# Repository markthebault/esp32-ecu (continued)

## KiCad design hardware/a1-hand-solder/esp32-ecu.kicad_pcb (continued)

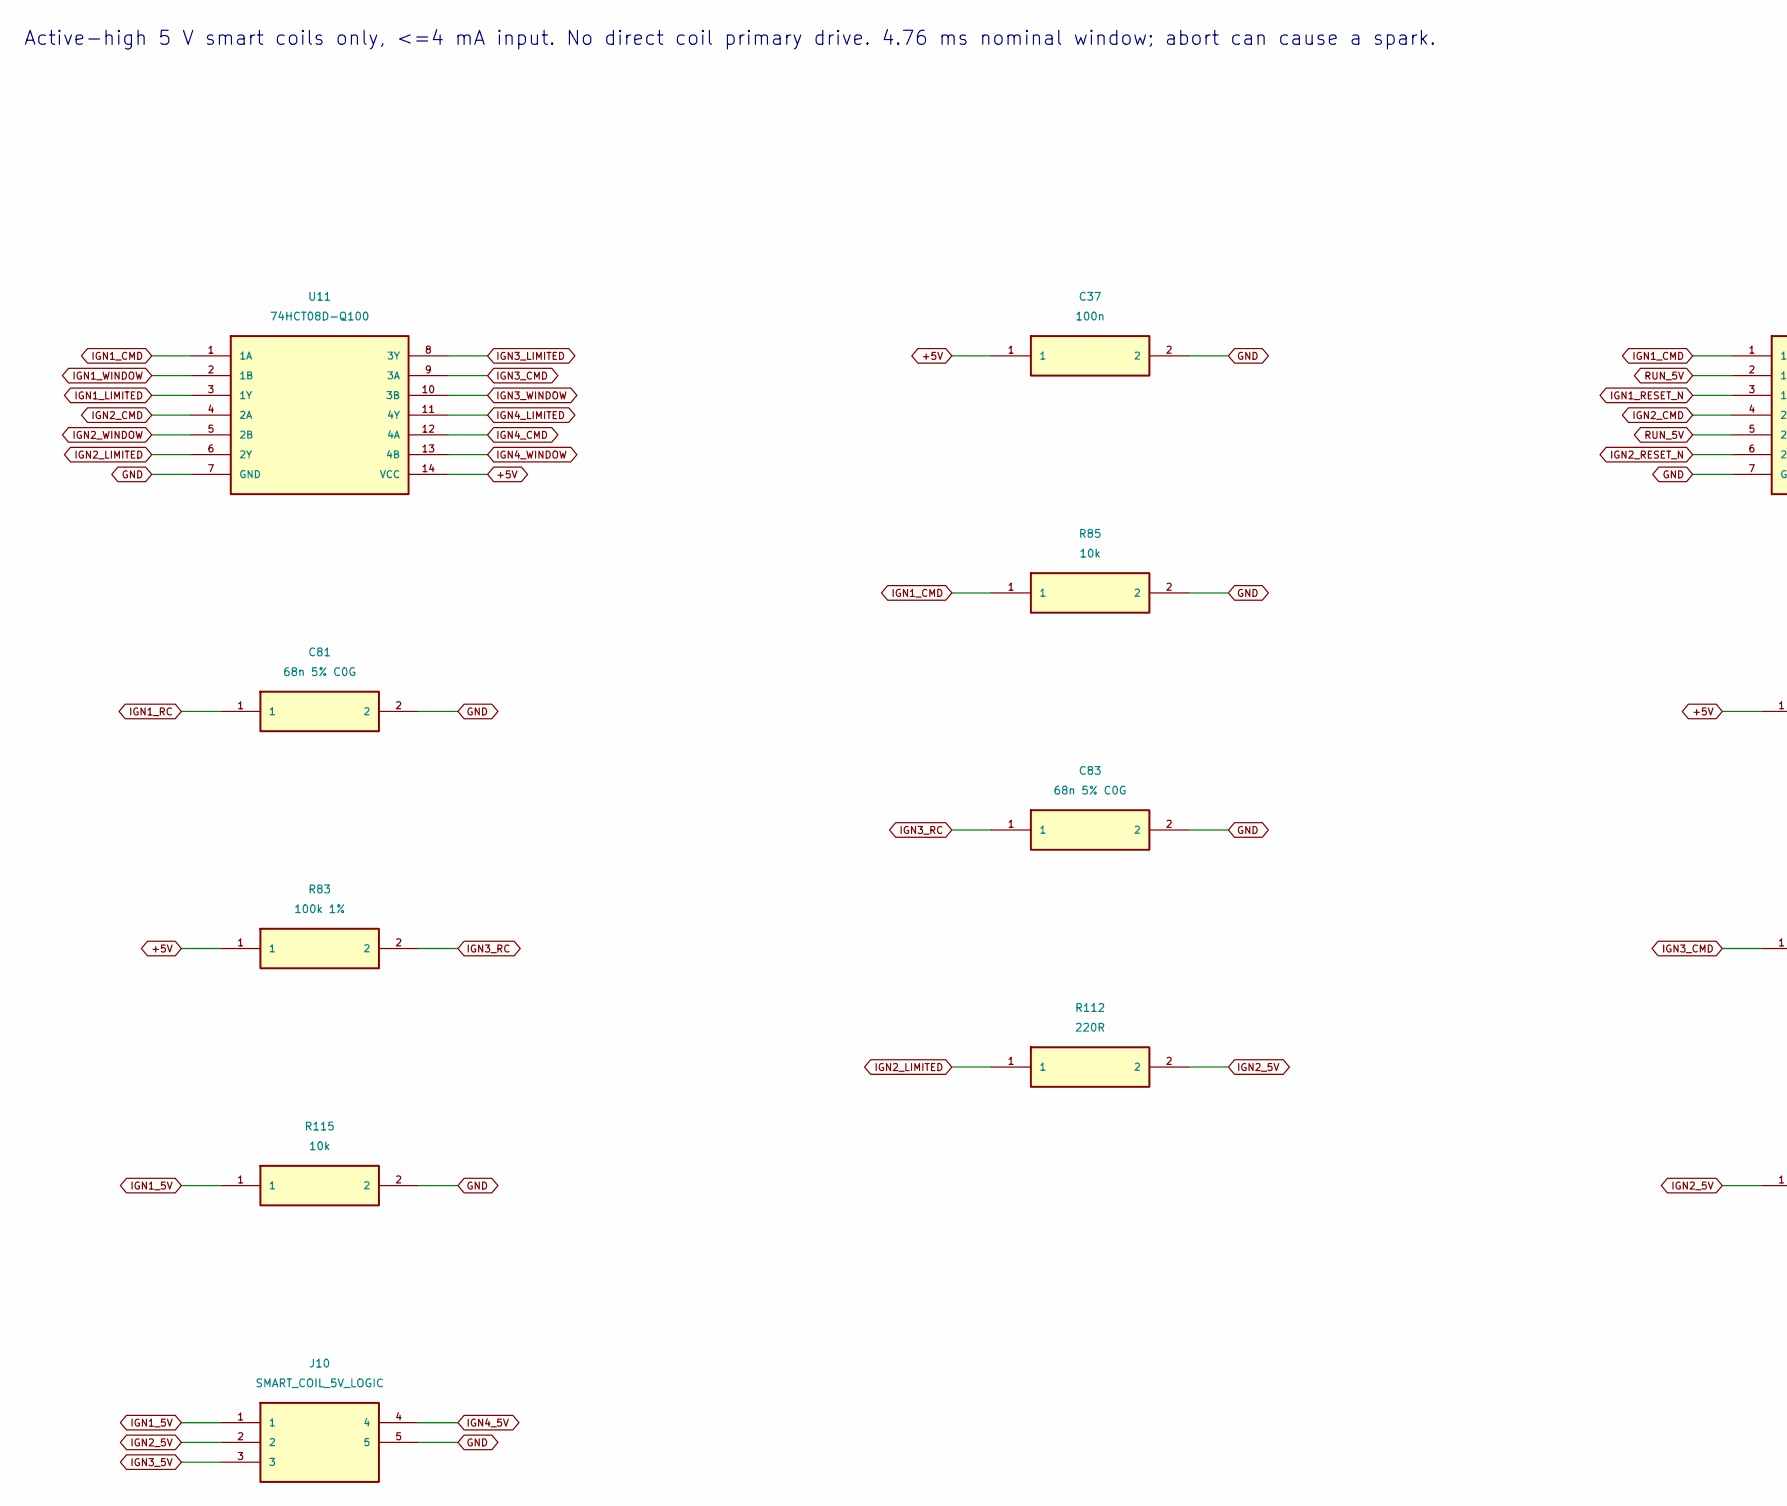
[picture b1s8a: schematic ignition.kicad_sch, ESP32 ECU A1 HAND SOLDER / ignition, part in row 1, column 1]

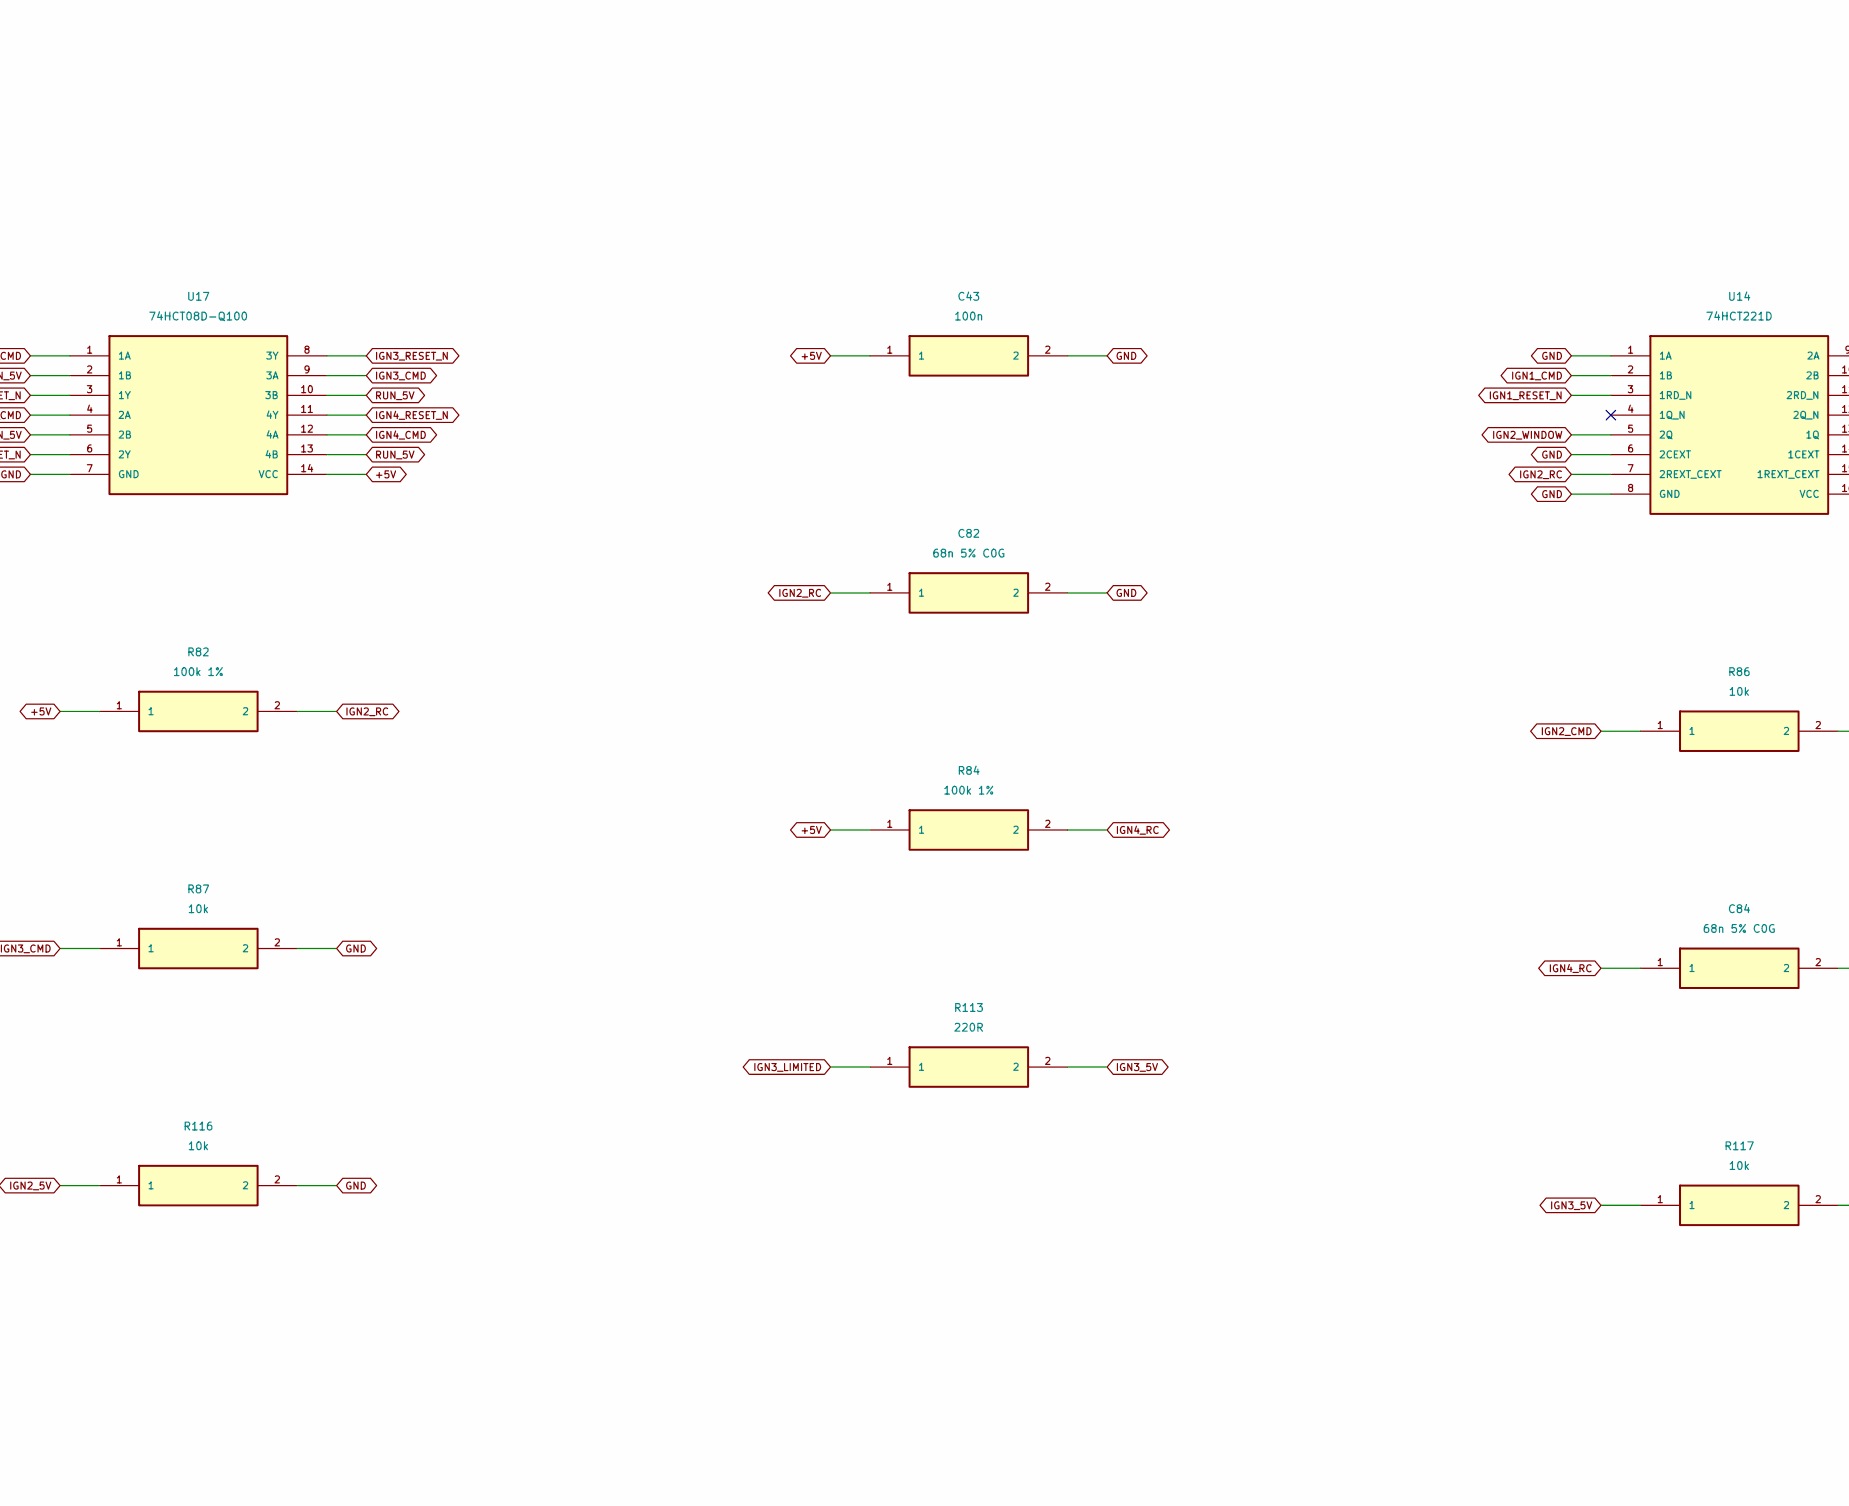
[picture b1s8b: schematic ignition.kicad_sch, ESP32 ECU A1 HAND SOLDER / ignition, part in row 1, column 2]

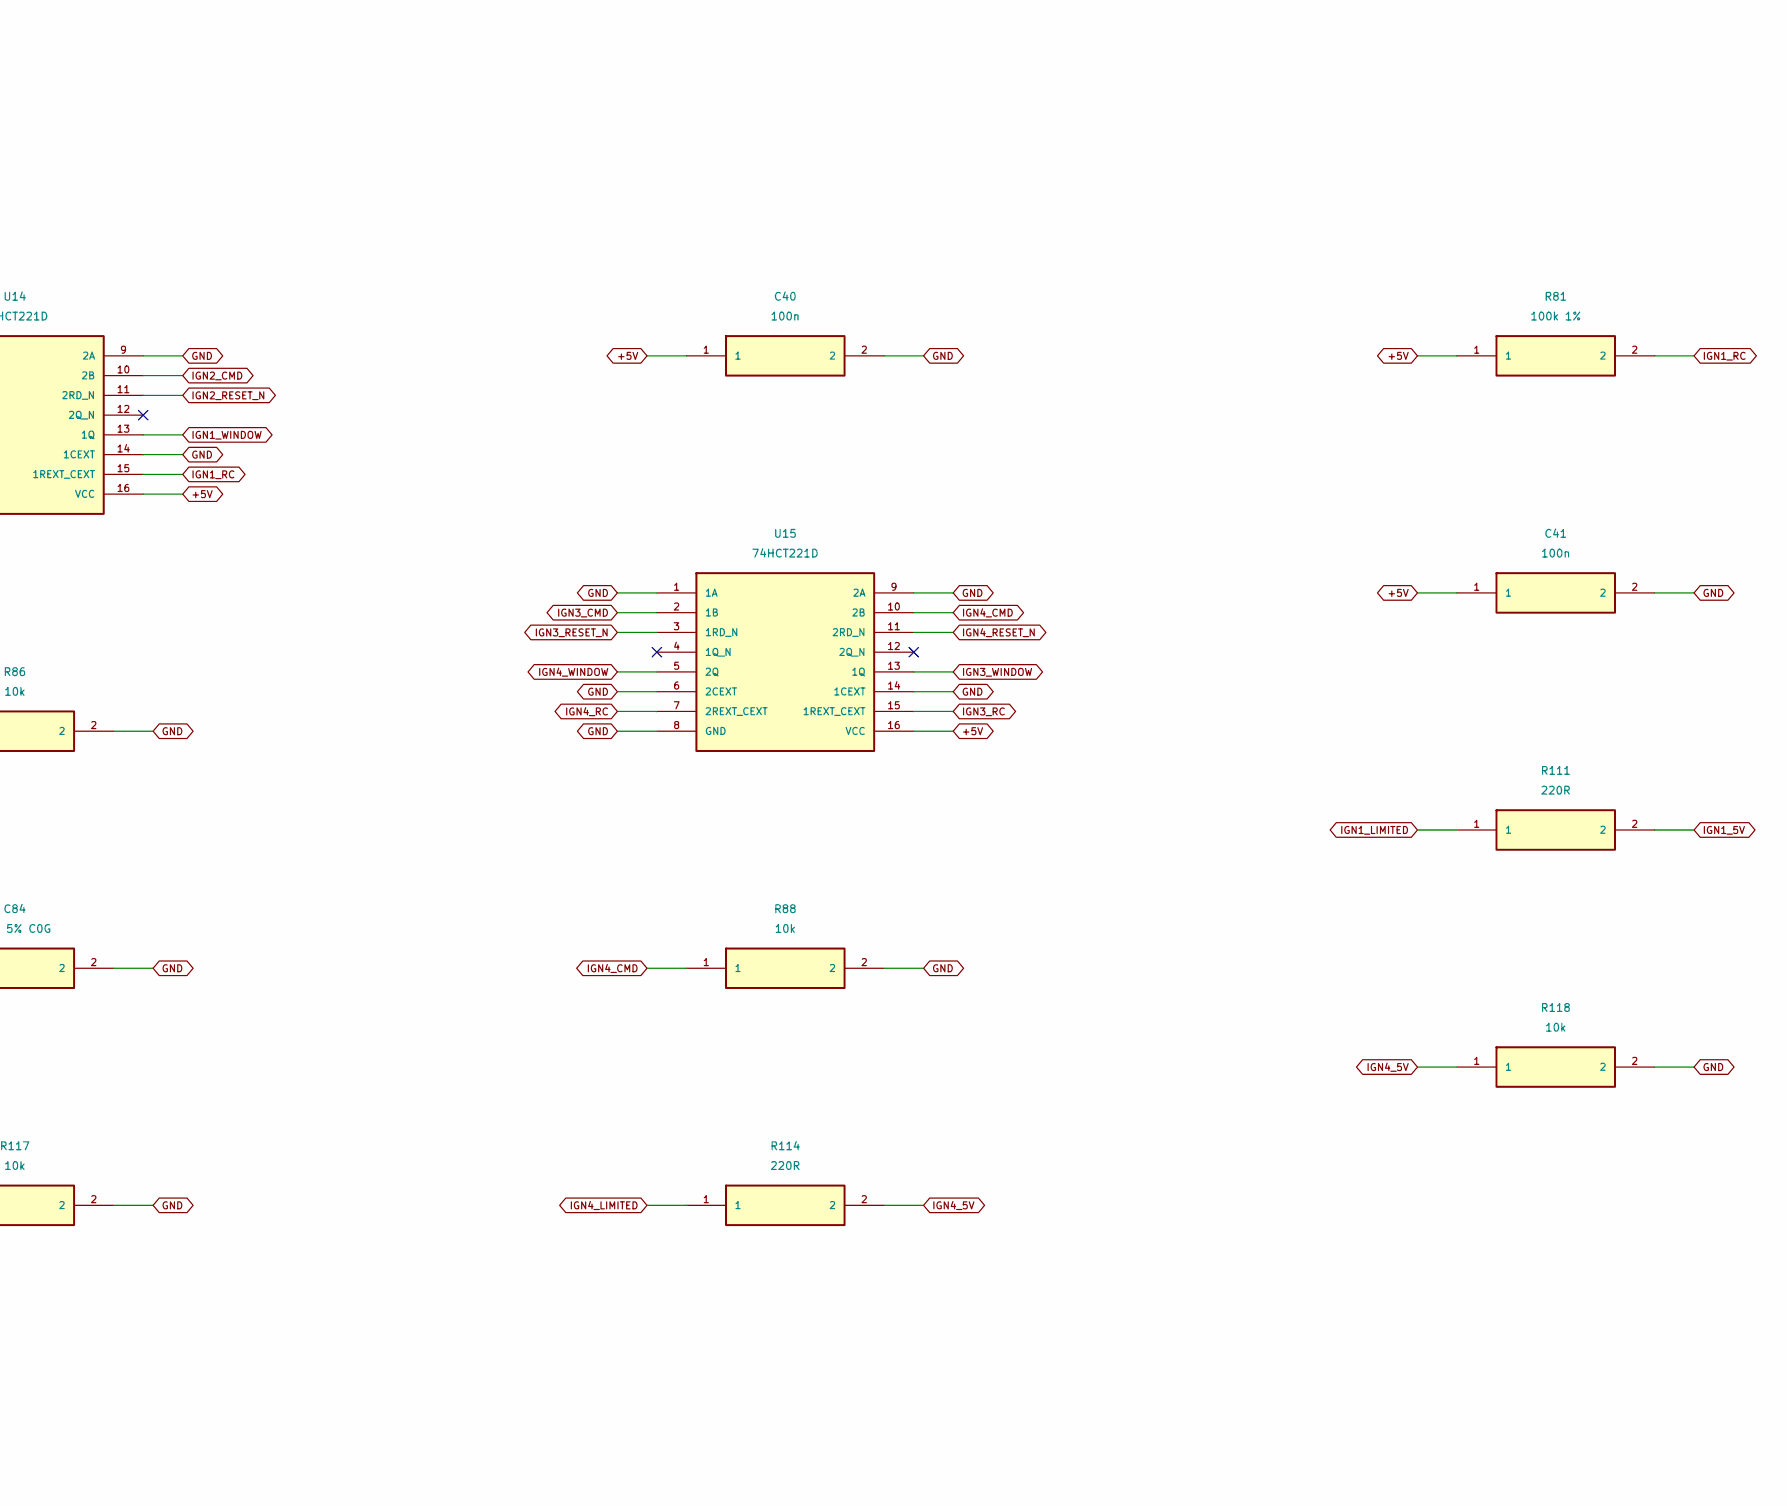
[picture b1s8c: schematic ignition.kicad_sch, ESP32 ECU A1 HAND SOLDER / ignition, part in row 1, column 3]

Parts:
C37, C40, C41, C43: 100n; C_1206_3216Metric_Pad1.33x1.80mm_HandSolder
C81, C82, C83, C84: 68n 5% C0G; C_1206_3216Metric_Pad1.33x1.80mm_HandSolder
J10: SMART_COIL_5V_LOGIC; JST_VH_B5P-VH_1x05_P3.96mm_Vertical; MPN B5P-VH(LF)(SN)
R81, R82, R83, R84: 100k 1%; R_1206_3216Metric_Pad1.30x1.75mm_HandSolder
R85, R86, R87, R88, R115, R116, R117, R118: 10k; R_1206_3216Metric_Pad1.30x1.75mm_HandSolder
R111, R112, R113, R114: 220R; R_1206_3216Metric_Pad1.30x1.75mm_HandSolder
U11, U17: 74HCT08D-Q100; SOIC-14_3.9x8.7mm_P1.27mm; MPN 74HCT08D-Q100,118
U14, U15: 74HCT221D; SOIC-16_3.9x9.9mm_P1.27mm; MPN 74HCT221D,118

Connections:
+5V: C37.1, C40.1, C41.1, C43.1, R81.1, R82.1, R83.1, R84.1, U11.14 (VCC), U14.16 (VCC), U15.16 (VCC), U17.14 (VCC); also elsewhere on the board
GND: C37.2, C40.2, C41.2, C43.2, C81.2, C82.2, C83.2, C84.2, J10.5, R85.2, R86.2, R87.2, R88.2, R115.2, R116.2, R117.2, R118.2, U11.7 (GND), U14.1 (1A), U14.6 (2CEXT), U14.8 (GND), U14.9 (2A), U14.14 (1CEXT), U15.1 (1A), U15.6 (2CEXT), U15.8 (GND), U15.9 (2A), U15.14 (1CEXT), U17.7 (GND); also elsewhere on the board
IGN1_5V: J10.1, R111.2, R115.1
IGN1_CMD: R85.1, U11.1 (1A), U14.2 (1B), U17.1 (1A); also elsewhere on the board
IGN1_LIMITED: R111.1, U11.3 (1Y)
IGN1_RC: C81.1, R81.2, U14.15 (1REXT_CEXT)
IGN1_RESET_N: U14.3 (1RD_N), U17.3 (1Y)
IGN1_WINDOW: U11.2 (1B), U14.13 (1Q)
IGN2_5V: J10.2, R112.2, R116.1
IGN2_CMD: R86.1, U11.4 (2A), U14.10 (2B), U17.4 (2A); also elsewhere on the board
IGN2_LIMITED: R112.1, U11.6 (2Y)
IGN2_RC: C82.1, R82.2, U14.7 (2REXT_CEXT)
IGN2_RESET_N: U14.11 (2RD_N), U17.6 (2Y)
IGN2_WINDOW: U11.5 (2B), U14.5 (2Q)
IGN3_5V: J10.3, R113.2, R117.1
IGN3_CMD: R87.1, U11.9 (3A), U15.2 (1B), U17.9 (3A); also elsewhere on the board
IGN3_LIMITED: R113.1, U11.8 (3Y)
IGN3_RC: C83.1, R83.2, U15.15 (1REXT_CEXT)
IGN3_RESET_N: U15.3 (1RD_N), U17.8 (3Y)
IGN3_WINDOW: U11.10 (3B), U15.13 (1Q)
IGN4_5V: J10.4, R114.2, R118.1
IGN4_CMD: R88.1, U11.12 (4A), U15.10 (2B), U17.12 (4A); also elsewhere on the board
IGN4_LIMITED: R114.1, U11.11 (4Y)
IGN4_RC: C84.1, R84.2, U15.7 (2REXT_CEXT)
IGN4_RESET_N: U15.11 (2RD_N), U17.11 (4Y)
IGN4_WINDOW: U11.13 (4B), U15.5 (2Q)
RUN_5V: U17.2 (1B), U17.5 (2B), U17.10 (3B), U17.13 (4B); also elsewhere on the board

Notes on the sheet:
Active-high 5 V smart coils only, <=4 mA input. No direct coil primary drive. 4.76 ms nominal window; abort can cause a spark.

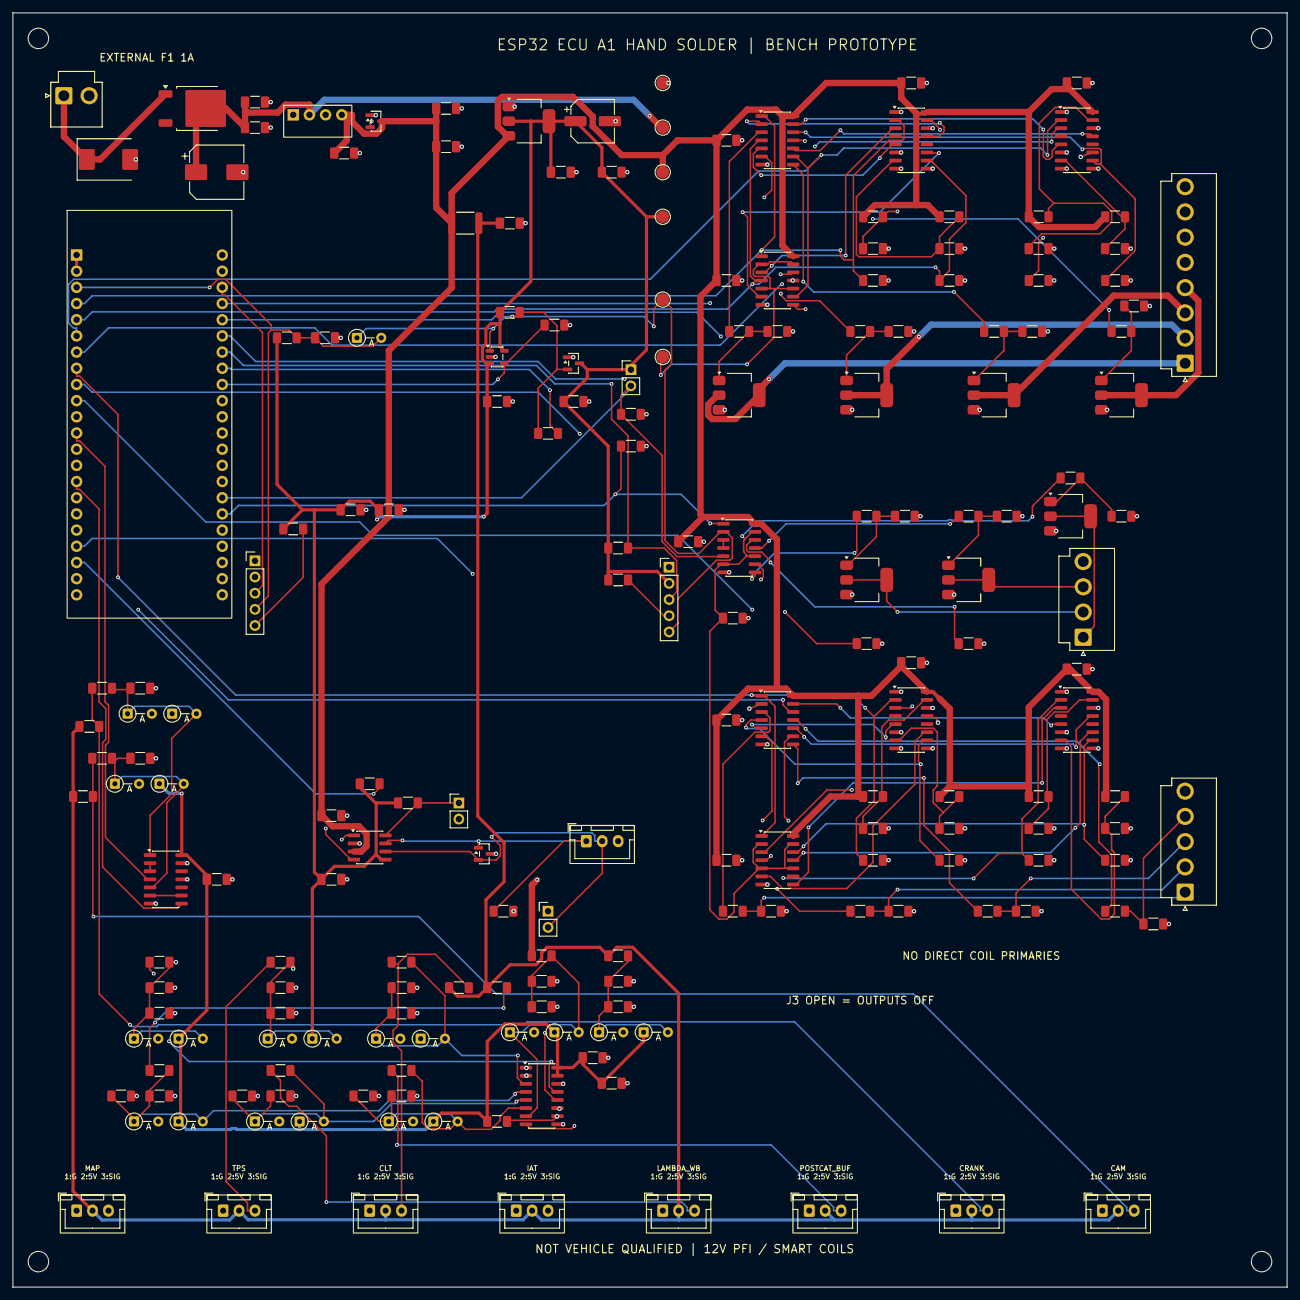
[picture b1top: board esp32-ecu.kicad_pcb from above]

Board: 4 copper layers, 200.0 x 200.0 mm, 201 parts (0 on the bottom side), 113 nets.

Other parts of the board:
H1, H2, H3, H4: M3 NPTH; MountingHole_3.2mm_M3

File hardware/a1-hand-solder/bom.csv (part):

Reference,Value,MPN,Footprint,DNP,Note
J1,FUSED_KEY_12V,B2P-VH(LF)(SN),Connector_JST:JST_VH_B2P-VH_1x02_P3.96mm_Vertical,False,Polarized internal loom connector. Separate fused relay-switched actuator supply. See pinout.
D1,SMCJ24CA,SMCJ24CA-E3/57T,Diode_SMD:D_SMC,False,"Bidirectional TVS. 24 V standoff; 38.9 V specified pulse clamp, not load-dump qualification."
D2,STPS5H100BY,STPS5H100BY,Package_TO_SOT_SMD:TO-252-2,False,100 V series reverse-polarity blocking diode; check forward loss and pulse stress.
C1,47u 63V,,Capacitor_SMD:CP_Elec_8x10,False,"Electrolytic, exact series must be qualified."
C2,2.2u 100V X7R,,Capacitor_SMD:C_1206_3216Metric_Pad1.33x1.80mm_HandSolder,False,
C3,100n 100V,,Capacitor_SMD:C_1206_3216Metric_Pad1.33x1.80mm_HandSolder,False,
U1,Pololu D36V6F5,Pololu 3792,ECU:Pololu_D36V6F5_vertical,False,A1 hand-solder revision; see docs/hand-solder.md
C5,22u 16V X7R,,Capacitor_SMD:C_1206_3216Metric_Pad1.33x1.80mm_HandSolder,False,
C6,22u 16V X7R,,Capacitor_SMD:C_1206_3216Metric_Pad1.33x1.80mm_HandSolder,False,
U2,NCV1117ST33T3G,NCV1117ST33T3G,Package_TO_SOT_SMD:SOT-223-3_TabPin2,False,Thermal budget <=200 mA continuous pending measurement. Requires output ESR review.
C9,22u 10V ESR 0.3-1R,,Capacitor_SMD:CP_Elec_6.3x5.8,False,Select exact electrolytic series to satisfy LDO stability over temperature.
C10,100n,,Capacitor_SMD:C_1206_3216Metric_Pad1.33x1.80mm_HandSolder,False,
R7,100R 0.25W,,Resistor_SMD:R_1206_3216Metric_Pad1.30x1.75mm_HandSolder,False,33 mA rail bleed provides a sink for fault clamp current. Must validate unpowered injection.
F2,PTC 100mA,MF-MSMF010-2,Fuse:Fuse_1812_4532Metric,False,"Resettable fuse, slow thermal response; no precision current limit."
C11,1u,,Capacitor_SMD:C_1206_3216Metric_Pad1.33x1.80mm_HandSolder,False,
U3,ESP32-S3-DevKitC-1-N8R8 v1.1,ESP32-S3-DevKitC-1-N8R8,ECU:ESP32_S3_DevKitC_1_socket,False,A1 hand-solder revision; see docs/hand-solder.md
R8,10k,,Resistor_SMD:R_1206_3216Metric_Pad1.30x1.75mm_HandSolder,False,
C12,1u,,Capacitor_SMD:C_1206_3216Metric_Pad1.33x1.80mm_HandSolder,False,
D3,BAT85,"BAT85,113",Diode_THT:D_DO-35_SOD27_P3.81mm_Vertical_AnodeUp,False,Axial Schottky mounted vertically. Validate input clamp voltage/leakage at temperature.
C13,10u,,Capacitor_SMD:C_1206_3216Metric_Pad1.33x1.80mm_HandSolder,False,
C14,100n,,Capacitor_SMD:C_1206_3216Metric_Pad1.33x1.80mm_HandSolder,False,
R9,10k,,Resistor_SMD:R_1206_3216Metric_Pad1.30x1.75mm_HandSolder,False,
J2,UART_FLASH_3V3_ONLY,,Connector_PinHeader_2.54mm:PinHeader_1x05_P2.54mm_Vertical,False,"External USB UART, 3.3 V logic. Supply board via J1; no USB backfeed."
U4,TPS3828-33DBVR,TPS3828-33DBVR,Package_TO_SOT_SMD:SOT-23-5,False,A1 hand-solder revision; see docs/hand-solder.md
R11,10k,,Resistor_SMD:R_1206_3216Metric_Pad1.30x1.75mm_HandSolder,False,
R12,100k,,Resistor_SMD:R_1206_3216Metric_Pad1.30x1.75mm_HandSolder,False,
C15,100n,,Capacitor_SMD:C_1206_3216Metric_Pad1.33x1.80mm_HandSolder,False,
U5,TLV803EA30DBZR,TLV803EA30DBZR,Package_TO_SOT_SMD:SOT-23,False,
C16,100n,,Capacitor_SMD:C_1206_3216Metric_Pad1.33x1.80mm_HandSolder,False,
R13,1k,,Resistor_SMD:R_1206_3216Metric_Pad1.30x1.75mm_HandSolder,False,
J3,NORMALLY_OPEN_INTERLOCK,,Connector_PinHeader_2.54mm:PinHeader_1x02_P2.54mm_Vertical,False,Fit only on supervised dummy-load bench. Open contact forces output inhibit independent of MCU.
R14,10k,,Resistor_SMD:R_1206_3216Metric_Pad1.30x1.75mm_HandSolder,False,
R15,10k,,Resistor_SMD:R_1206_3216Metric_Pad1.30x1.75mm_HandSolder,False,
J4,EXPANSION_3V3,,Connector_PinHeader_2.54mm:PinHeader_1x05_P2.54mm_Vertical,False,
R16,4.7k,,Resistor_SMD:R_1206_3216Metric_Pad1.30x1.75mm_HandSolder,False,
R17,4.7k,,Resistor_SMD:R_1206_3216Metric_Pad1.30x1.75mm_HandSolder,False,
R20,22k 1%,,Resistor_SMD:R_1206_3216Metric_Pad1.30x1.75mm_HandSolder,False,
R21,33k 1%,,Resistor_SMD:R_1206_3216Metric_Pad1.30x1.75mm_HandSolder,False,
C20,10n,,Capacitor_SMD:C_1206_3216Metric_Pad1.33x1.80mm_HandSolder,False,
D100,BAT85,"BAT85,113",Diode_THT:D_DO-35_SOD27_P3.81mm_Vertical_AnodeUp,False,Axial Schottky mounted vertically. Validate input clamp voltage/leakage at temperature.
D101,BAT85,"BAT85,113",Diode_THT:D_DO-35_SOD27_P3.81mm_Vertical_AnodeUp,False,Axial Schottky mounted vertically. Validate input clamp voltage/leakage at temperature.
R22,22k 1%,,Resistor_SMD:R_1206_3216Metric_Pad1.30x1.75mm_HandSolder,False,
R23,33k 1%,,Resistor_SMD:R_1206_3216Metric_Pad1.30x1.75mm_HandSolder,False,
C21,10n,,Capacitor_SMD:C_1206_3216Metric_Pad1.33x1.80mm_HandSolder,False,
D110,BAT85,"BAT85,113",Diode_THT:D_DO-35_SOD27_P3.81mm_Vertical_AnodeUp,False,Axial Schottky mounted vertically. Validate input clamp voltage/leakage at temperature.
D111,BAT85,"BAT85,113",Diode_THT:D_DO-35_SOD27_P3.81mm_Vertical_AnodeUp,False,Axial Schottky mounted vertically. Validate input clamp voltage/leakage at temperature.
R24,22k 1%,,Resistor_SMD:R_1206_3216Metric_Pad1.30x1.75mm_HandSolder,False,
R25,33k 1%,,Resistor_SMD:R_1206_3216Metric_Pad1.30x1.75mm_HandSolder,False,
C22,10n,,Capacitor_SMD:C_1206_3216Metric_Pad1.33x1.80mm_HandSolder,False,
D120,BAT85,"BAT85,113",Diode_THT:D_DO-35_SOD27_P3.81mm_Vertical_AnodeUp,False,Axial Schottky mounted vertically. Validate input clamp voltage/leakage at temperature.
D121,BAT85,"BAT85,113",Diode_THT:D_DO-35_SOD27_P3.81mm_Vertical_AnodeUp,False,Axial Schottky mounted vertically. Validate input clamp voltage/leakage at temperature.
R26,22k 1%,,Resistor_SMD:R_1206_3216Metric_Pad1.30x1.75mm_HandSolder,False,
R27,33k 1%,,Resistor_SMD:R_1206_3216Metric_Pad1.30x1.75mm_HandSolder,False,
C23,10n,,Capacitor_SMD:C_1206_3216Metric_Pad1.33x1.80mm_HandSolder,False,
D130,BAT85,"BAT85,113",Diode_THT:D_DO-35_SOD27_P3.81mm_Vertical_AnodeUp,False,Axial Schottky mounted vertically. Validate input clamp voltage/leakage at temperature.
D131,BAT85,"BAT85,113",Diode_THT:D_DO-35_SOD27_P3.81mm_Vertical_AnodeUp,False,Axial Schottky mounted vertically. Validate input clamp voltage/leakage at temperature.
R28,22k 1%,,Resistor_SMD:R_1206_3216Metric_Pad1.30x1.75mm_HandSolder,False,
R29,33k 1%,,Resistor_SMD:R_1206_3216Metric_Pad1.30x1.75mm_HandSolder,False,
C24,10n,,Capacitor_SMD:C_1206_3216Metric_Pad1.33x1.80mm_HandSolder,False,
D140,BAT85,"BAT85,113",Diode_THT:D_DO-35_SOD27_P3.81mm_Vertical_AnodeUp,False,Axial Schottky mounted vertically. Validate input clamp voltage/leakage at temperature.
D141,BAT85,"BAT85,113",Diode_THT:D_DO-35_SOD27_P3.81mm_Vertical_AnodeUp,False,Axial Schottky mounted vertically. Validate input clamp voltage/leakage at temperature.
R30,22k 1%,,Resistor_SMD:R_1206_3216Metric_Pad1.30x1.75mm_HandSolder,False,
R31,33k 1%,,Resistor_SMD:R_1206_3216Metric_Pad1.30x1.75mm_HandSolder,False,
C25,10n,,Capacitor_SMD:C_1206_3216Metric_Pad1.33x1.80mm_HandSolder,False,
D150,BAT85,"BAT85,113",Diode_THT:D_DO-35_SOD27_P3.81mm_Vertical_AnodeUp,False,Axial Schottky mounted vertically. Validate input clamp voltage/leakage at temperature.
D151,BAT85,"BAT85,113",Diode_THT:D_DO-35_SOD27_P3.81mm_Vertical_AnodeUp,False,Axial Schottky mounted vertically. Validate input clamp voltage/leakage at temperature.
R32,2.49k 1% NTC,,Resistor_SMD:R_1206_3216Metric_Pad1.30x1.75mm_HandSolder,True,Populate only for passive NTC sensor; transfer curve must match selected sensor.
R33,2.49k 1% NTC,,Resistor_SMD:R_1206_3216Metric_Pad1.30x1.75mm_HandSolder,True,Populate only for passive NTC sensor; transfer curve must match selected sensor.
R34,120k 1%,,Resistor_SMD:R_1206_3216Metric_Pad1.30x1.75mm_HandSolder,False,
R35,10k 1%,,Resistor_SMD:R_1206_3216Metric_Pad1.30x1.75mm_HandSolder,False,
C26,10n,,Capacitor_SMD:C_1206_3216Metric_Pad1.33x1.80mm_HandSolder,False,
D160,BAT85,"BAT85,113",Diode_THT:D_DO-35_SOD27_P3.81mm_Vertical_AnodeUp,False,Axial Schottky mounted vertically. Validate input clamp voltage/leakage at temperature.
D161,BAT85,"BAT85,113",Diode_THT:D_DO-35_SOD27_P3.81mm_Vertical_AnodeUp,False,Axial Schottky mounted vertically. Validate input clamp voltage/leakage at temperature.
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
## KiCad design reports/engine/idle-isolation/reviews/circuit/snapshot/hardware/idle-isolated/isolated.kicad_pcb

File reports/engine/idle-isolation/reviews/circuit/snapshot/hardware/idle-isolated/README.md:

# IAC-DRAFT2 isolated idle interface

This separate **90 × 60 mm, two-layer THT draft** replaces the IAC-DRAFT1 development path. It has routed copper and native ERC/DRC/connectivity/parity checks, with independent review and conditional circuit experiments in [the evidence](../../reports/engine/idle-isolation/). **Fabrication and powered valve integration remain on hold.** Every shipped firmware environment still disables physical idle writes. Nothing here qualifies a real engine, vehicle, isolation voltage, thermal behavior or enclosure fit.

Use the [native project](isolated.kicad_pro), [schematic](isolated.kicad_sch), [net contract](net_contract.json), [PCB BOM](bom.csv), [harness addendum](harness-bom.csv) and [footprint provenance](footprint-provenance.json). All fitted electrical parts are leaded. DIP devices solder directly, without sockets. NT1 is an unfitted copper connection at the MOSFET source, not an SMD part. Four unplated M3 holes have 82 × 52 mm centres. The older [IAC-DRAFT1](../idle-accessory/) and A3/A4 sources remain historical records.

| Connection | Pin order, PCB top view |
| --- | --- |
| J1, XH4 input | 1 IDLE_CMD; 2 RUN_5V; 3 CARRIER_5V; 4 CARRIER_GND |
| A5 J21, PH4 | 1 IDLE_CMD/GPIO3; 2 RUN_5V; 3 +5V; 4 GND. Harness maps 1→1 through 4→4 to accessory J1 |
| J2, fixed screw terminal | 1 separate externally protected, fused, relay-switched 9–16 V; 2 dedicated actuator return |
| J3, VH2 valve | 1 valve positive; 2 IAC_LS |

J1 and J3 deliberately use different connector families, and J2 uses a fixed screw terminal. Inspect the actual keyed mating view and continuity before power; a wire-side drawing may be mirrored. The new PH header is only on the separate [A5 carrier](../a5-idle-interface/README.md). Do not assume it exists on an A3/A4 board. Carrier J1 and sensor rails cannot supply the valve.

Two input-side 2N3904BU buffers drive the LEDs of two Vishay 6N137 DIP8 optocouplers. Carrier power/return reach only those buffers and LEDs. The detector side has its own LM317AT supply, MCP100-485DI/TO supervisor, SN74HCT02N NOR and UCC27524P.B gate driver. Both command and hardware RUN LEDs must conduct for a valid high command. Supervisor ENA and its 4.7 kΩ pulldown operate independently of that NOR. The 120/374 Ω 1% divider has a calculated DC range of 4.967–5.346 V under the declared datasheet assumptions. That calculation does not bound startup, overshoot, load transients or temperature of an assembly.

The driver switches an IRLZ44NPBF through 33 Ω, with 10 kΩ gate-to-source bias. SB5H100 flyback has its cathode/band at valve positive and anode at the drain. The intended valve is **two-wire, normally closed, energize-to-open, continuous PWM, actual current ≤2 A across 9–16 V and temperature**. There is no current limit, thermal shutdown, valve position/current feedback or separate valve-supply measurement on this draft. The firmware battery value is only a proxy. A drain-source short can energize a normal-current coil without blowing a fuse. An independently operable actuator-branch disconnect is required and remains to be specified and tested.

**Combined RUN drive remains a release hold:** U9 also supplies carrier R47/R50/R53, Q7 and ten HCT inputs. Buffered LEDs do not establish the loaded RUN voltage. R2 is now 2.2 kΩ; the ST 500 µA Q7 figure applies at 10 V/25°C, with a different fault-sink case. Measure actual RUN/MAIN_IN, startup, temperature and fault loading before powered integration.

## Assembly and return routing

The optical barrier has a 5 mm copper-free rule area. Do not bridge it with wires, flux contamination, case foil, a heatsink, mounting hardware or test equipment. This is low-voltage return separation, without a certified isolation rating.

ACT_GND carries coil current directly from Q1 source to J2. LOGIC_GND joins it only through NT1 at the Q1 source copper; it has a separate Kelvin path to U1. Do not add a second logic-to-power ground strap. A return open must not divert coil current into the carrier harness.

**C1–C5, C10, R13 and R14 mount on the back.** C4 is the local 100 nF bypass; C10 is the nearby 1 µF driver bulk capacitor. Their short seeded connections and the source-star path must survive any reroute. U1/U4 front silk outlines are omitted where back-component holes pass underneath; the fabrication layer, courtyard and pin1 marks remain. Read the side in the contract and fabrication drawings, rather than inferring placement from silk alone.

Assemble the front low-profile parts first, trim/inspect their soldered leads before fitting the back parts, and inspect the opposite-side leads before fitting each DIP. Back components and their lead ends must clear front bodies, solder joints and insulating supports. Do not solder a DIP over an uninspected lead end. Exact leaded capacitor/resistor selections, back-component height, lead trim, standoff height and enclosure clearance require a real assembly trial. The old A3 case/ZIP is not a fit model for this additional board. Both TO220 tabs are live at different potentials: Q1 is drain; U6 is regulator output. Do not share an uninsulated heatsink or contact the lining. Stock 1.10 mm TO220 holes have little diagonal lead margin; verify finished holes and the actual procured leads before fabrication approval.

## Debugging and outstanding acceptance

With all power removed, verify the harness pin order, diode/electrolytic polarity, no unintended carrier-to-actuator conductive path and no second LOGIC_GND/ACT_GND join. Use ordinary continuity measurements, not a megohmmeter through electronics. Verify the permanent A5 R154 bias even with J21 unplugged. Read actual GPIO3/JTAG eFuse routing without burning eFuses. Socket pitch, actual N16R8 geometry and antenna RF clearance remain unmeasured.

The first powered experiment must use a current-limited resistor fixture, with an independent actuator cutoff and appropriate isolated/differential measurement. Preserve protective earth; connecting ordinary scope ground clips across the barrier would defeat this experiment. Observe:

| Probe | Reference / interpretation |
| --- | --- |
| J1 pins1/2/3 | J1 pin4, carrier domain. Measure loaded GPIO, RUN and LED supply |
| U2/U3 LED current | Voltage across R3/R4 divided by actual resistance; temperature/storage timing unqualified |
| U6 output / U5 pin1 / U1 ENA | LOGIC_GND. Record startup, reset, rail dropout and release delay |
| U1 VDD/GND | Across pins6/3 at the package. Observe local bypass ringing |
| Q1 gate / drain | Relative to Q1 source, with correct probe isolation/rating |
| J2 return / J1 return | Separate current observations, including deliberately opened returns |

Capture cold startup, reset/download, RUN low, lost command, watchdog/interlock, J1 disconnects, each supply/return open and recovery. Test 0/100%, the actual minimum accepted 1 µs pulse and the full PWM range. A 40 µs test alone cannot establish the 1 µs path. The MCP100 assertion delay has no specified maximum; its 10 µs typical value is not a brownout guarantee. The exact procured UCC27524P/P.B guarantee, opto loading, GPIO levels, passive parts, valve R/L, independent disconnect, protected branch, power-loop temperature, rail stability and real mounting/sealing all remain release items. No board was flashed to enable idle.

Reproduction commands, simulation limitations and review closure are in [the idle hardware guide](../../docs/engine-idle-isolation.md). No manufacturing files are exported from this draft.

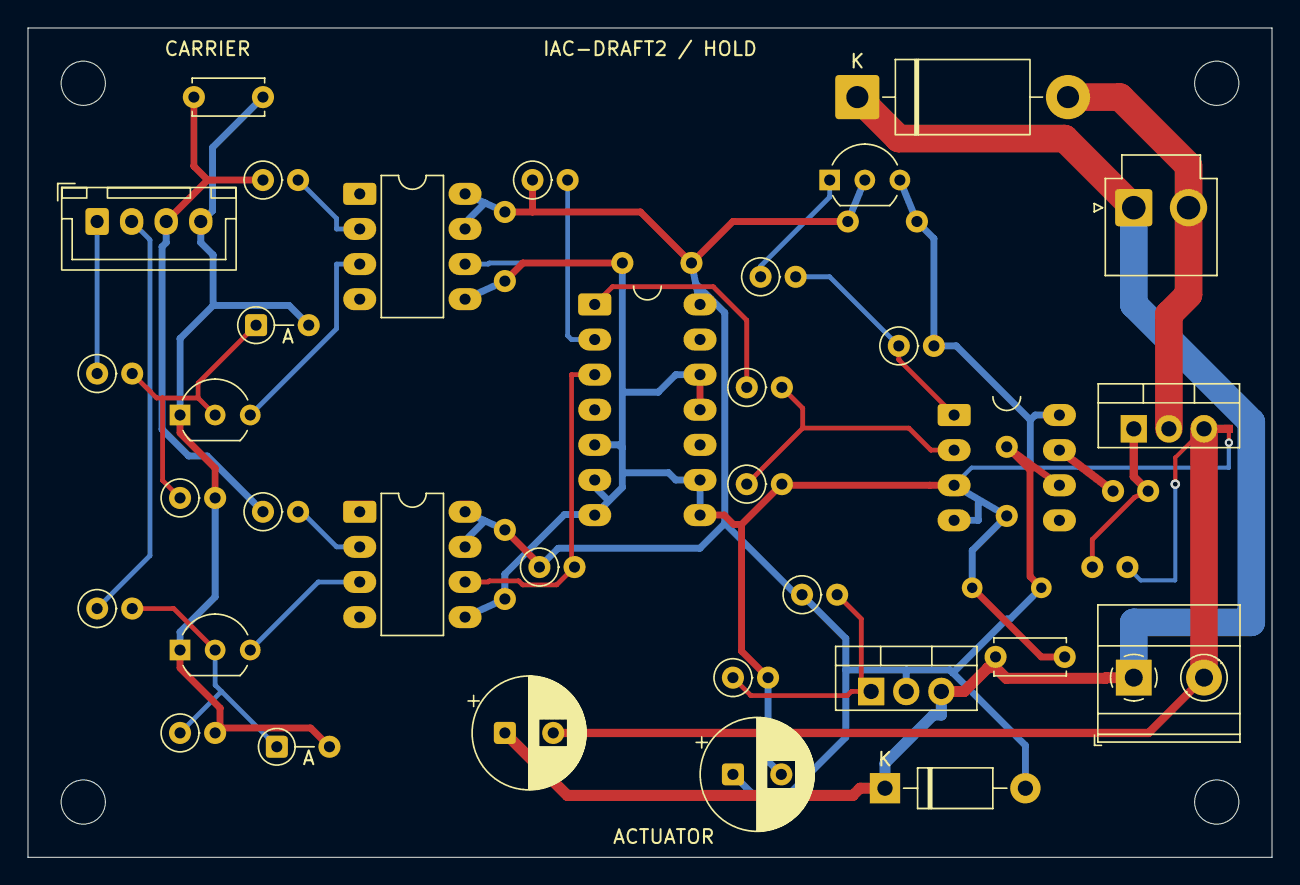
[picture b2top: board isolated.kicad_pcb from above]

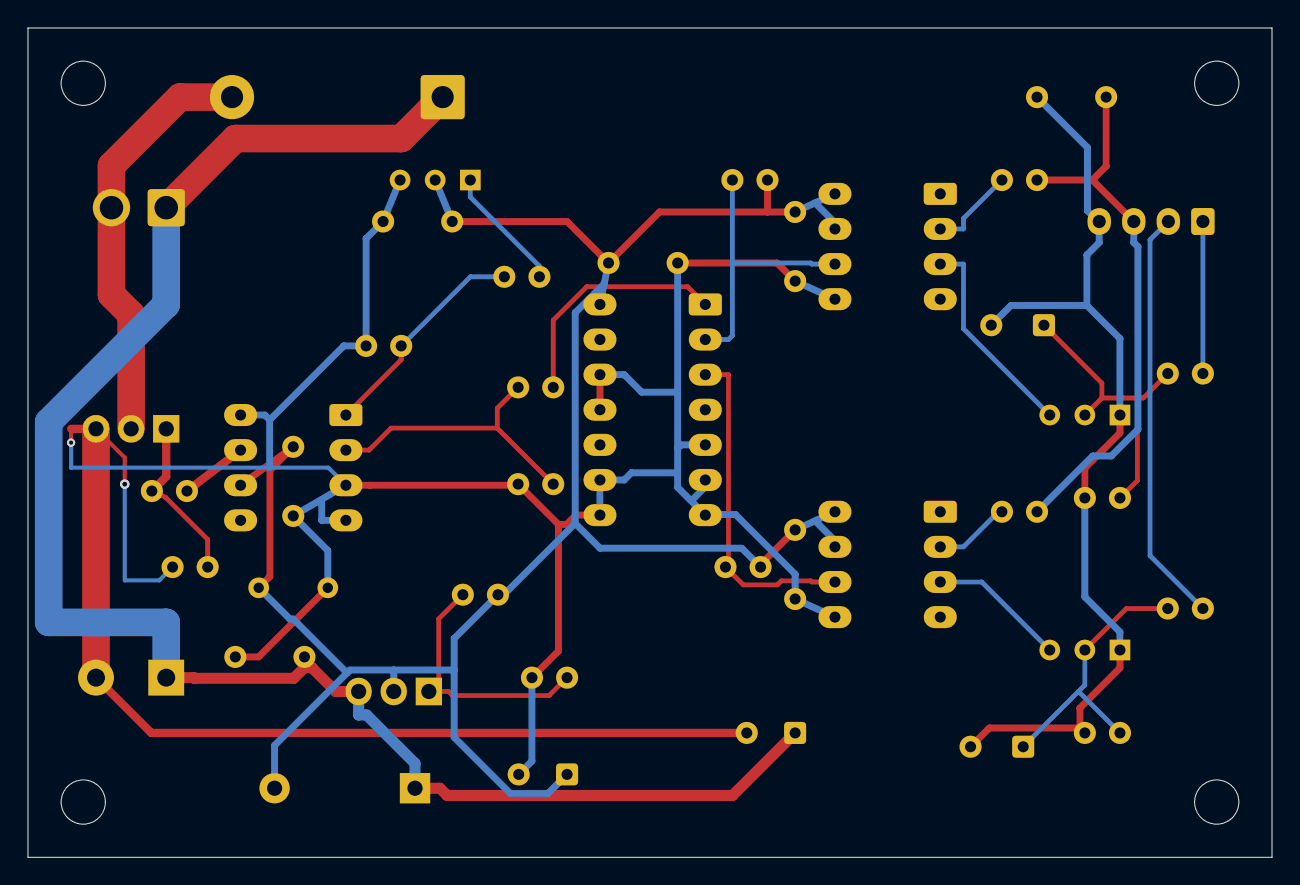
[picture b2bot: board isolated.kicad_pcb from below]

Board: 2 copper layers, 90.0 x 60.0 mm, 47 parts (8 on the bottom side), 24 nets.

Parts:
C1, C2, C3, C4, C5: 100nF 50V; C_Disc_D5.0mm_W2.5mm_P5.00mm_BackAssembly
C6: 100uF 50V; CP_Radial_D8.0mm_P3.50mm
C7: 22uF 16V; CP_Radial_D8.0mm_P3.50mm
C8, C9: 100nF 50V; C_Disc_D5.0mm_W2.5mm_P5.00mm
C10: 1uF 16V+ FILM; C_Rect_L7.2mm_W5.0mm_P5.00mm_BackAssembly
D1: SB5H100-E3; D_DO-201AD_P15.24mm_Horizontal
D2: 1N4007; D_DO-41_SOD81_P10.16mm_Horizontal
D3, D4: 1N4148; D_DO-35_SOD27_P3.81mm_Vertical_AnodeUp
H1, H2, H3, H4: M3 ISOLATED MOUNT; MountingHole_3.2mm_M3
J1: CARRIER INPUT DOMAIN; JST_XH_B4B-XH-A_1x04_P2.50mm_Vertical
J2: PROTECTED ACTUATOR SUPPLY; TerminalBlock_Phoenix_MKDS-1,5-2-5.08_1x02_P5.08mm_Horizont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
J3: NC TWO-WIRE VALVE; JST_VH_B2P-VH_1x02_P3.96mm_Vertical
NT1: SOURCE RETURN STAR / COPPER ONLY; NetTie_Source_Star
Q1: IRLZ44NPBF; TO-220-3_Vertical
Q2, Q3: 2N3904; TO-92_Inline_Wide
R1: 1k 1%; R_Axial_DIN0207_L6.3mm_D2.5mm_P2.54mm_Vertical
R2: 2k2 1%; R_Axial_DIN0207_L6.3mm_D2.5mm_P2.54mm_Vertical
R3, R4: 357R 1%; R_Axial_DIN0207_L6.3mm_D2.5mm_P2.54mm_Vertical
R5, R6: 100k; R_Axial_DIN0207_L6.3mm_D2.5mm_P2.54mm_Vertical
R7, R8, R9, R11: 1k; R_Axial_DIN0207_L6.3mm_D2.5mm_P2.54mm_Vertical
R10: 10k; R_Axial_DIN0207_L6.3mm_D2.5mm_P2.54mm_Vertical
R12: 4k7; R_Axial_DIN0207_L6.3mm_D2.5mm_P2.54mm_Vertical
R13: 33R; R_Axial_DIN0207_L6.3mm_D2.5mm_P2.54mm_Vertical_BackAssembly
R14: 10k; R_Axial_DIN0207_L6.3mm_D2.5mm_P2.54mm_Vertical_BackAssembly
R15: 120R 1%; R_Axial_DIN0207_L6.3mm_D2.5mm_P2.54mm_Vertical
R16: 374R 1%; R_Axial_DIN0207_L6.3mm_D2.5mm_P2.54mm_Vertical
U1: UCC27524P; DIP-8_W7.62mm_LongPads_BypassClearSilk
U2, U3: 6N137; DIP-8_W7.62mm_LongPads
U4: SN74HCT02N; DIP-14_W7.62mm_LongPads_BypassClearSilk
U5: MCP100-485DI/TO; TO-92_Inline_Wide
U6: LM317AT/NOPB; TO-220-3_Vertical

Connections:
ACT_5V2: C1.1, C2.1, C3.1, C4.1, C5.1, C7.1, C10.1, D2.2, R7.1, R8.1, R15.1, U1.6, U2.7, U2.8, U3.7, U3.8, U4.14, U5.2, U6.2
ACT_12V: C6.1, C8.1, D1.1, D2.1, J2.1, J3.1, U6.3
ACT_GND: C6.2, J2.2, NT1.1, Q1.3, R14.2
ADJ: R15.2, R16.1, U6.1
CARRIER_5V: C9.1, J1.3, R3.1, R4.1
CARRIER_GND: C9.2, D3.2, D4.2, J1.4, Q2.1, Q3.1, R5.2, R6.2
DRIVE: R13.1, U1.7
ENA: R11.2, R12.1, U1.1
GATE: Q1.1, R13.2, R14.1
IAC_LS: D1.2, J3.2, Q1.2
IDLE_CMD: J1.1, R1.1
INA: R9.2, R10.1, U1.2
LOCAL_OK: R11.1, U5.1
LOGIC_GND: C1.2, C2.2, C3.2, C4.2, C5.2, C7.2, C8.2, C10.2, NT1.2, R10.2, R12.2, R16.2, U1.3, U1.4, U1.8, U2.5, U3.5, U4.5, U4.6, U4.7, U4.8, U4.9, U4.11, U4.12, U5.3
PWM_BASE: D3.1, Q2.2, R1.2, R5.1
PWM_LED_A: R3.2, U2.2
PWM_LED_K: Q2.3, U2.3
PWM_N: R7.2, U2.6, U4.2
PWM_RUN: R9.1, U4.1
RUN_5V: J1.2, R2.1
RUN_BASE: D4.1, Q3.2, R2.2, R6.1
RUN_LED_A: R4.2, U3.2
RUN_LED_K: Q3.3, U3.3
RUN_N: R8.2, U3.6, U4.3
